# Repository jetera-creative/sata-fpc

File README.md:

# Tape-SATA Plug
SATA plugin board to lead the SATA FPC port on laptop motherboard out.

```
|                                         Power                                        |                SATA                 |
| -------------------------------------------------------------------------------------------------------------------------- |
| 12V | 12V | 12V | GND | GND | GND | 5V | 5G | 5V | GND | GND | GND | 3V3 | 3V3 | 3V3 | GND | B+ | B- | GND | A- | A+ | GND |
        |  |            |        |
        |  |            |        |
        |  |            |        |
BarrelJack (12V)        |  FPC   |
                        |        |
                        |        |
                        |        |
                        |        |
|      Power      |              SATA                |
| -------------------------------------------------- |
| 5V | 5V | 5V | GND | B+ | B- | GND | A- | A+ | GND |
```

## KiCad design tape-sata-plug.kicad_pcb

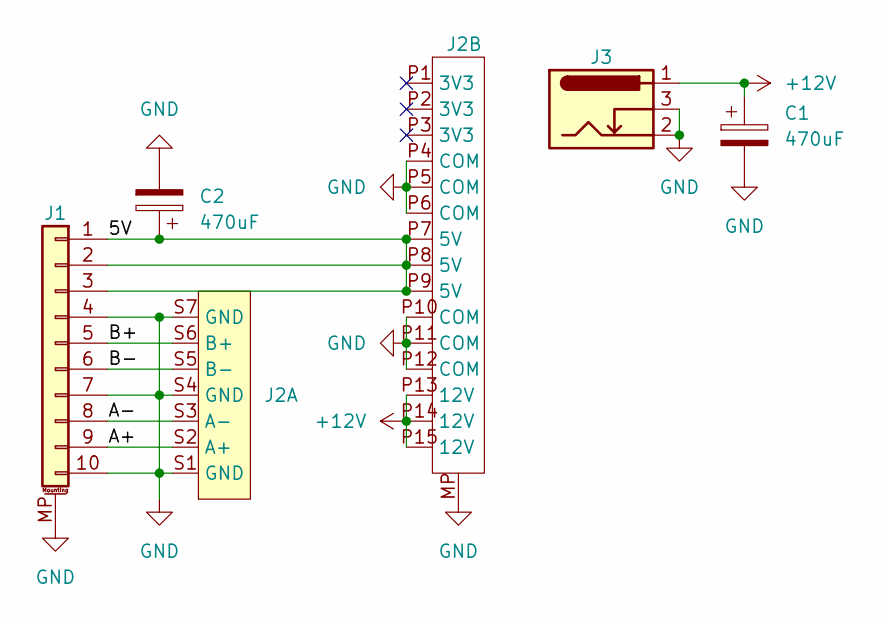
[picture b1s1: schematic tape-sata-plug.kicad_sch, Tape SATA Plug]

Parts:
C1, C2: 470uF; CP_Radial_D6.3mm_P2.50mm
J1: Conn_01x10_MountingPin; TE_1-1734839-0_1x10-1MP_P0.5mm_Horizontal
J2: SATA_Amphenol_10029364-001LF_Horizontal
J3: Barrel_Jack_Switch; BarrelJack_Horizontal

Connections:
+12V: C1.1, J2.P13 (12V), J2.P14 (12V), J2.P15 (12V), J3.1
/5V: C2.1, J1.1, J1.2, J1.3, J2.P7 (5V), J2.P8 (5V), J2.P9 (5V)
/A+: J1.9, J2.S2 (A+)
/A-: J1.8, J2.S3 (A-)
/B+: J1.5, J2.S6 (B+)
/B-: J1.6, J2.S5 (B-)
GND: C1.2, C2.2, J1.4, J1.7, J1.10, J1.MP (MountPin), J2.MP, J2.P4 (COM), J2.P5 (COM), J2.P6 (COM), J2.P10 (COM), J2.P11 (COM), J2.P12 (COM), J2.S1 (GND), J2.S4 (GND), J2.S7 (GND), J3.2, J3.3

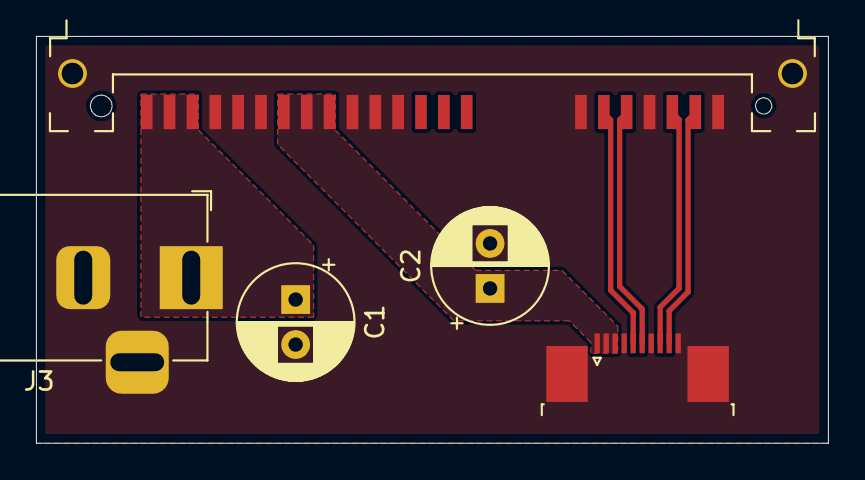
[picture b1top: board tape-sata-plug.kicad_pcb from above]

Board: 2 copper layers, 44.0 x 22.6 mm, 5 parts (0 on the bottom side), 7 nets.

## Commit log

2024-04-14 2024.1

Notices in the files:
tape-sata-plug.kicad_pcb:
https://creativecommons.org/licenses/by-sa/4.0/legalcode.en
Use of this schematic is governed under the CC BY-SA 4.0 International license.
